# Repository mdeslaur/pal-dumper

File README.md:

# PAL dumper

This is a small adapter board to read secured PALs as a 27C020 EPROM in a
device programmer.

This is based on the design from Charles MacDonald available here:

http://dreamjam.co.uk/emuviews/readpal.php

Gerbers for JLCPCB are in the gerbers directory.

Change history:  
1.0 - Initial version  

To Do:  

Marc Deslauriers
2022-09-18

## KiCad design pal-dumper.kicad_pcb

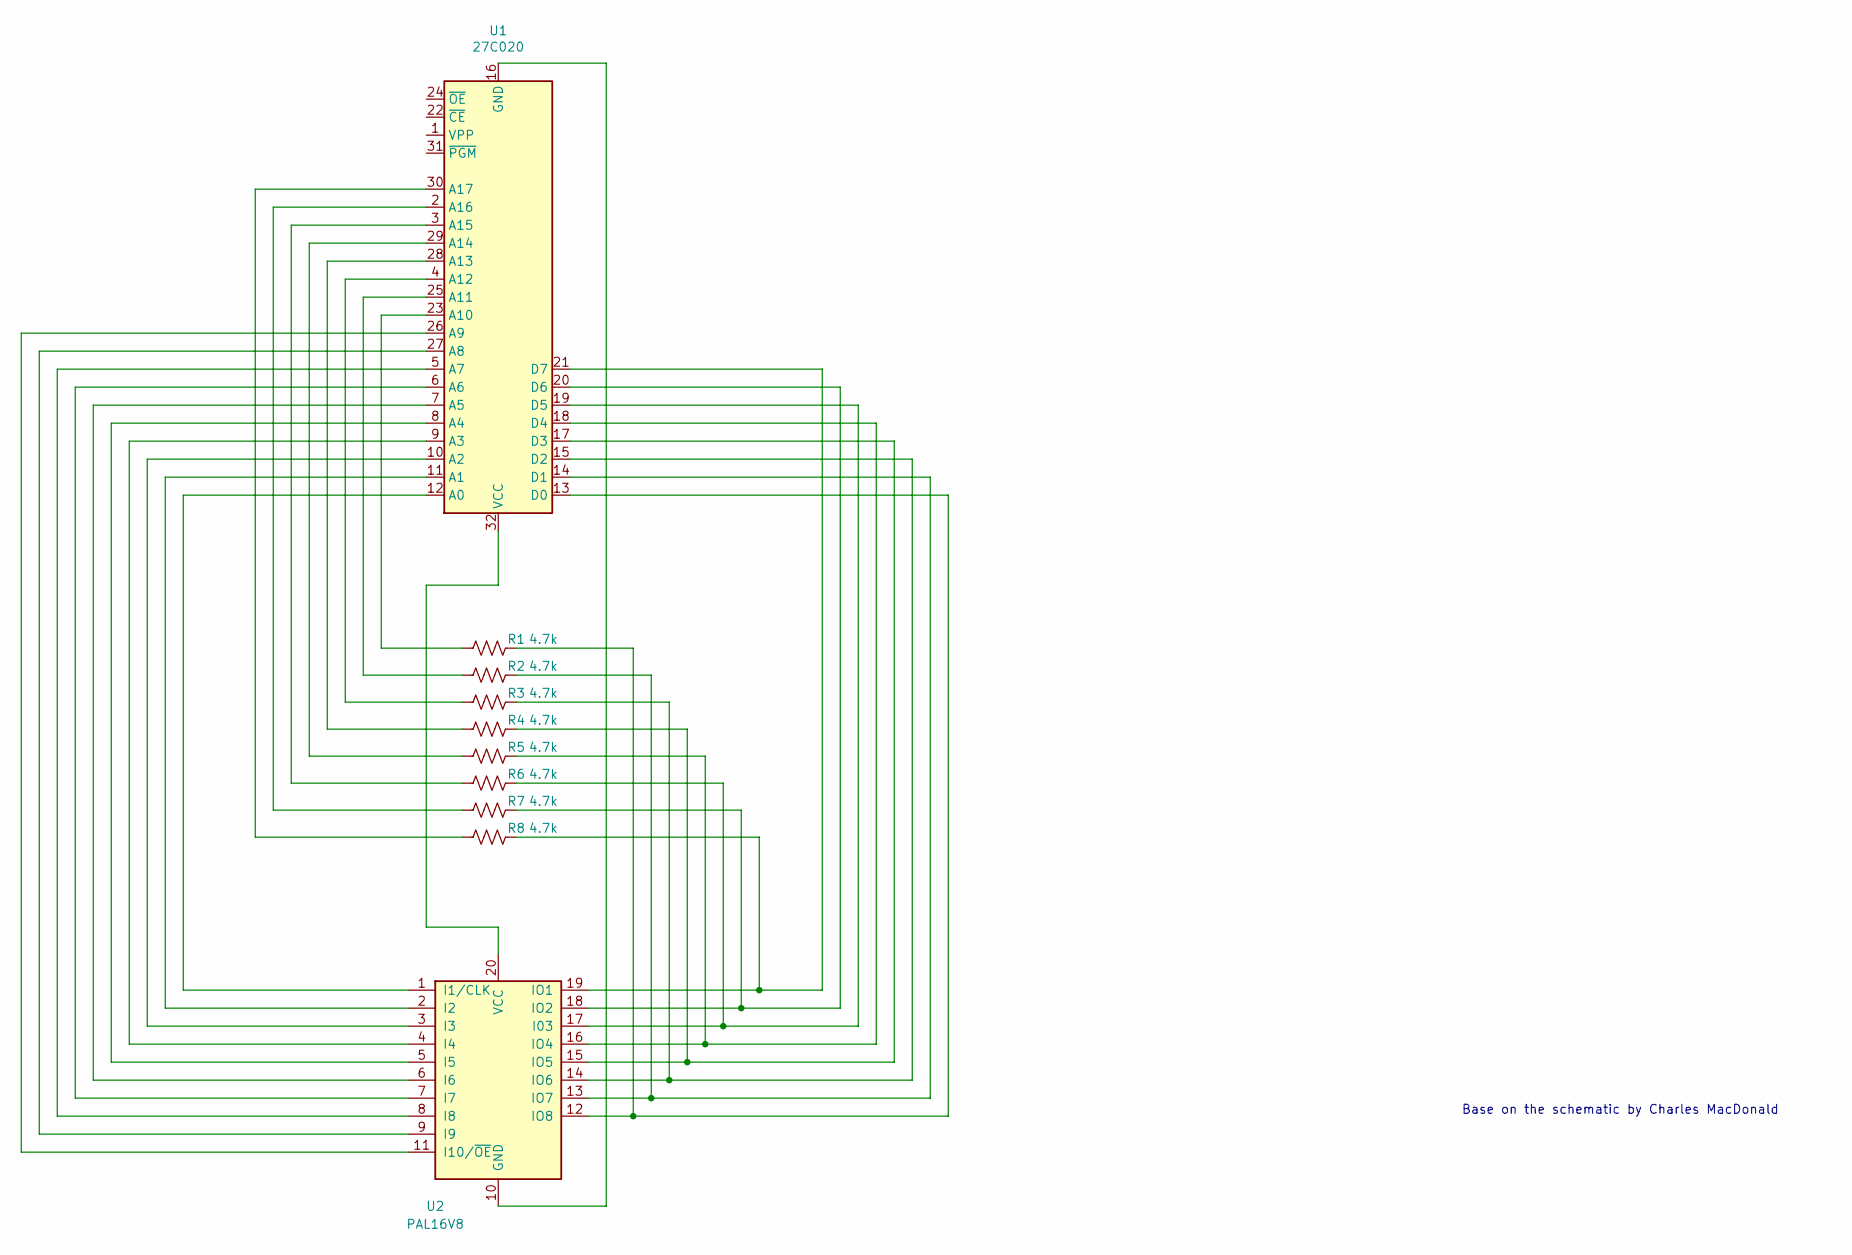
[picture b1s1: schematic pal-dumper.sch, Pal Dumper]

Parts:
R1, R2, R3, R4, R5, R6, R7, R8: 4.7k; R_Axial_DIN0207_L6.3mm_D2.5mm_P7.62mm_Horizontal
U1: 27C020; DIP-32_W15.24mm_Socket
U2: PAL16V8; DIP-20_W7.62mm_Socket

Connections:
unnamed: R1.1, U1.13 (D0), U2.12 (IO8)
unnamed: R1.2, U1.23 (A10)
unnamed: R2.1, U1.14 (D1), U2.13 (IO7)
unnamed: R2.2, U1.25 (A11)
unnamed: R3.1, U1.15 (D2), U2.14 (IO6)
unnamed: R3.2, U1.4 (A12)
unnamed: R4.1, U1.17 (D3), U2.15 (IO5)
unnamed: R4.2, U1.28 (A13)
unnamed: R5.1, U1.18 (D4), U2.16 (IO4)
unnamed: R5.2, U1.29 (A14)
unnamed: R6.1, U1.19 (D5), U2.17 (I03)
unnamed: R6.2, U1.3 (A15)
unnamed: R7.1, U1.20 (D6), U2.18 (IO2)
unnamed: R7.2, U1.2 (A16)
unnamed: R8.1, U1.21 (D7), U2.19 (IO1)
unnamed: R8.2, U1.30 (A17)
unnamed: U1.5 (A7), U2.8 (I8)
unnamed: U1.6 (A6), U2.7 (I7)
unnamed: U1.7 (A5), U2.6 (I6)
unnamed: U1.8 (A4), U2.5 (I5)
unnamed: U1.9 (A3), U2.4 (I4)
unnamed: U1.10 (A2), U2.3 (I3)
unnamed: U1.11 (A1), U2.2 (I2)
unnamed: U1.12 (A0), U2.1 (I1/CLK)
unnamed: U1.16 (GND), U2.10 (GND)
unnamed: U1.26 (A9), U2.11 (I10/~OE~)
unnamed: U1.27 (A8), U2.9 (I9)
unnamed: U1.32 (VCC), U2.20 (VCC)

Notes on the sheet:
Base on the schematic by Charles MacDonald

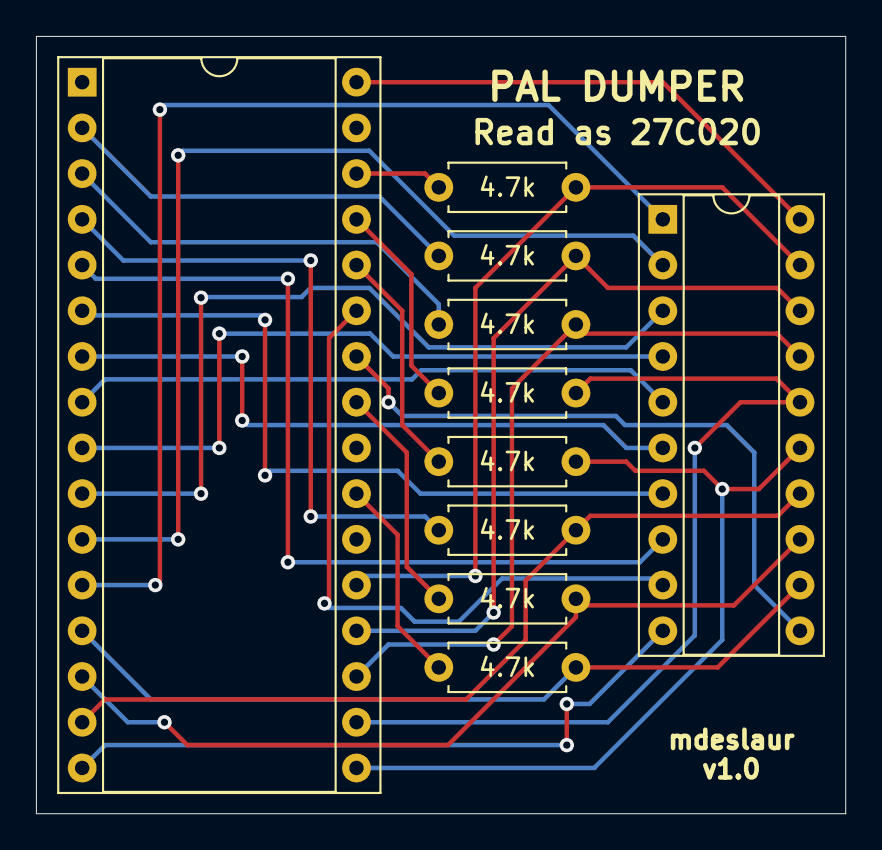
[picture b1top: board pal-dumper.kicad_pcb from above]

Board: 2 copper layers, 45.0 x 43.2 mm, 10 parts (0 on the bottom side), 28 nets.
